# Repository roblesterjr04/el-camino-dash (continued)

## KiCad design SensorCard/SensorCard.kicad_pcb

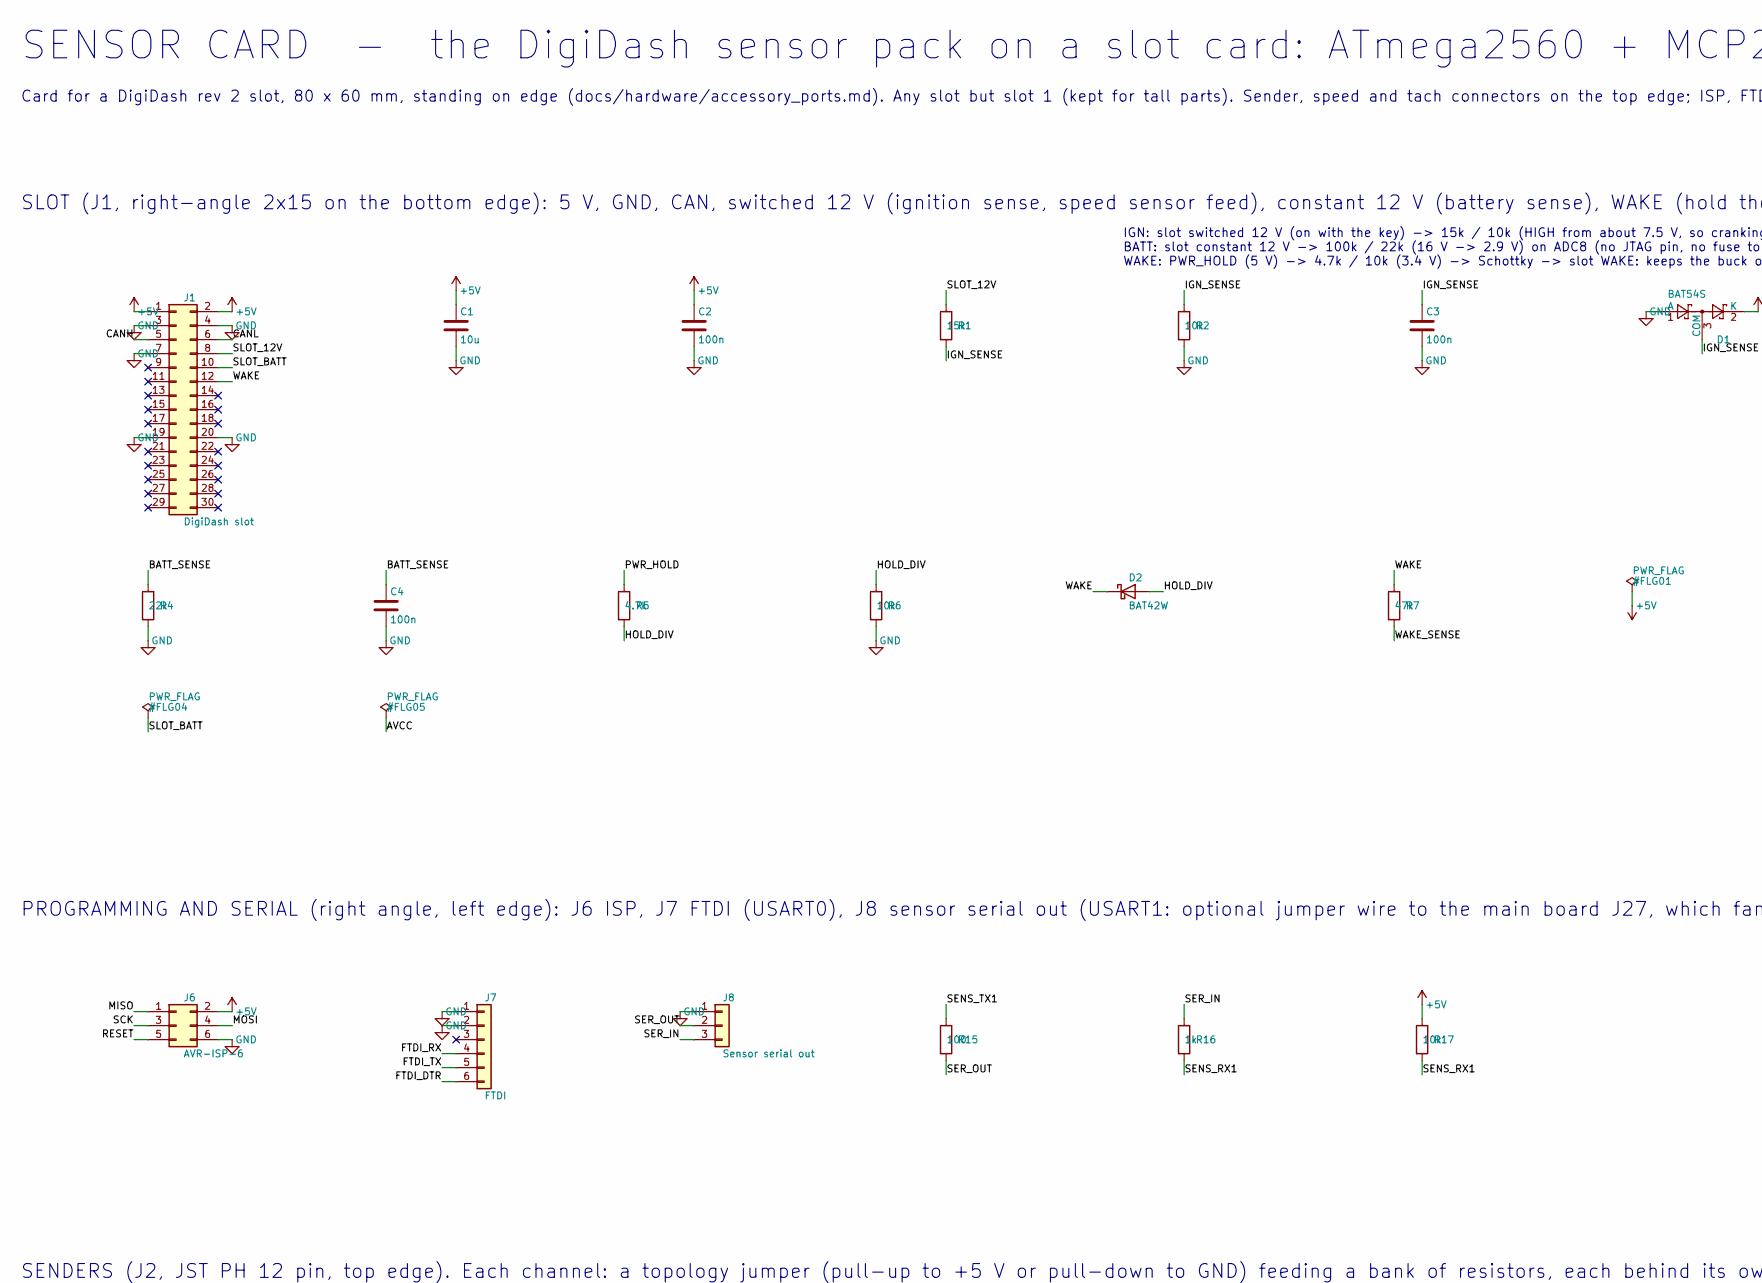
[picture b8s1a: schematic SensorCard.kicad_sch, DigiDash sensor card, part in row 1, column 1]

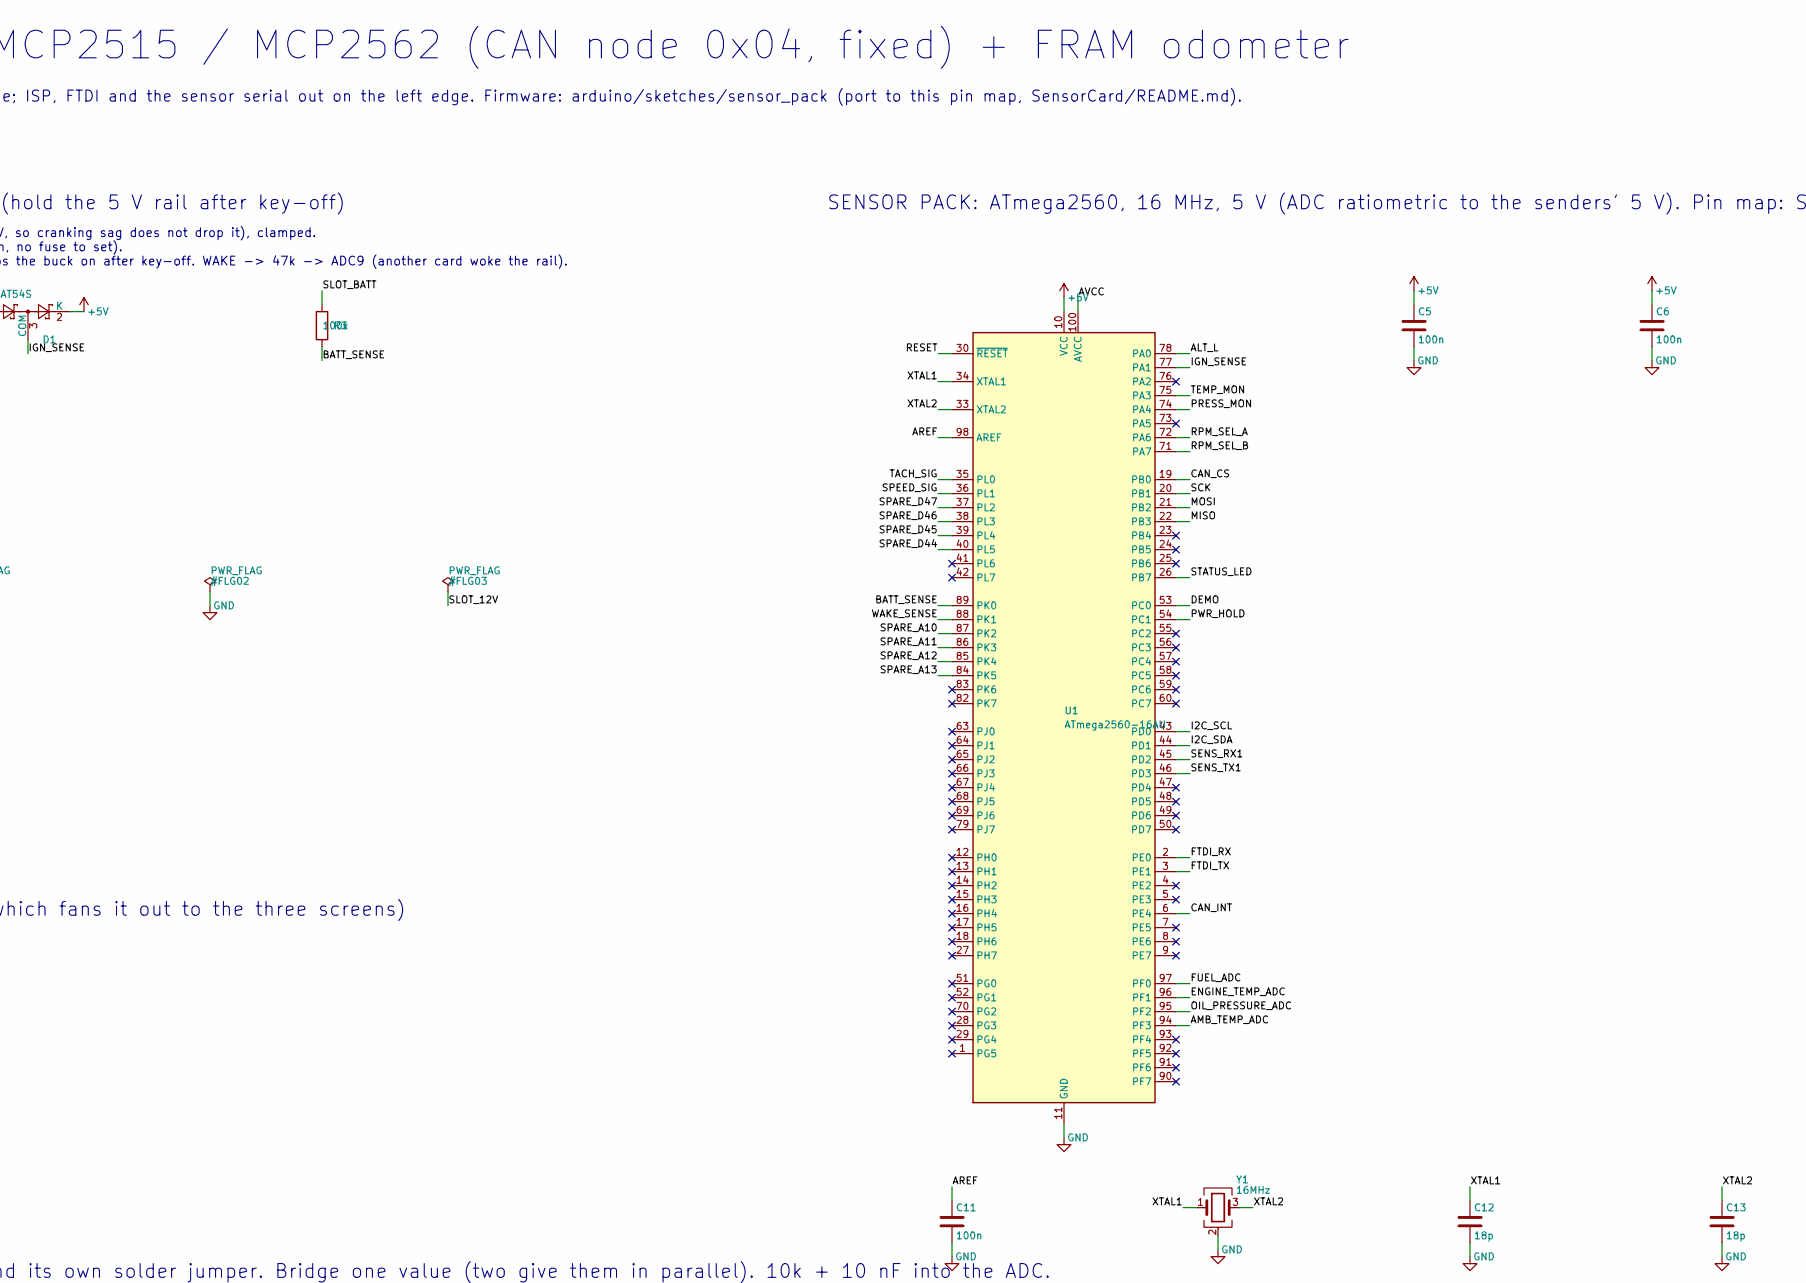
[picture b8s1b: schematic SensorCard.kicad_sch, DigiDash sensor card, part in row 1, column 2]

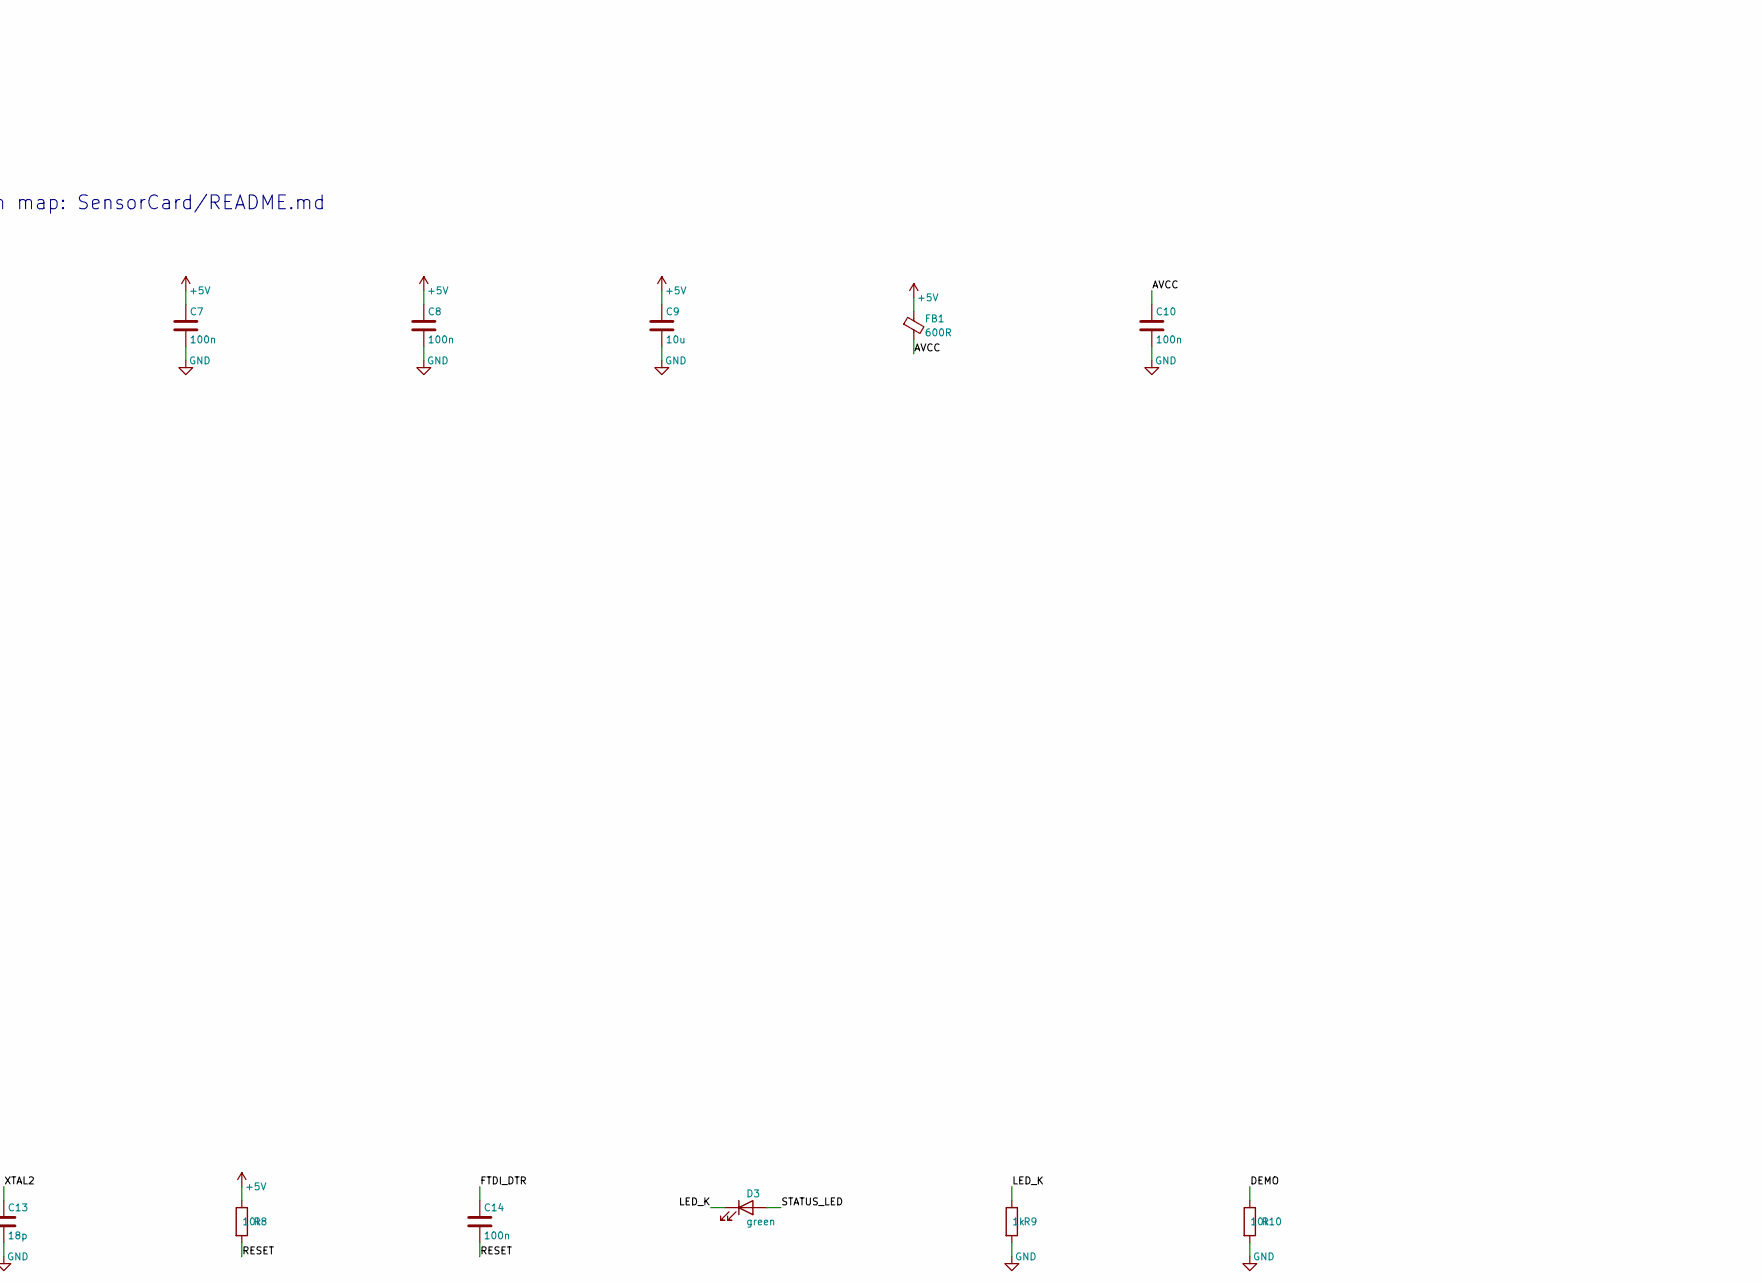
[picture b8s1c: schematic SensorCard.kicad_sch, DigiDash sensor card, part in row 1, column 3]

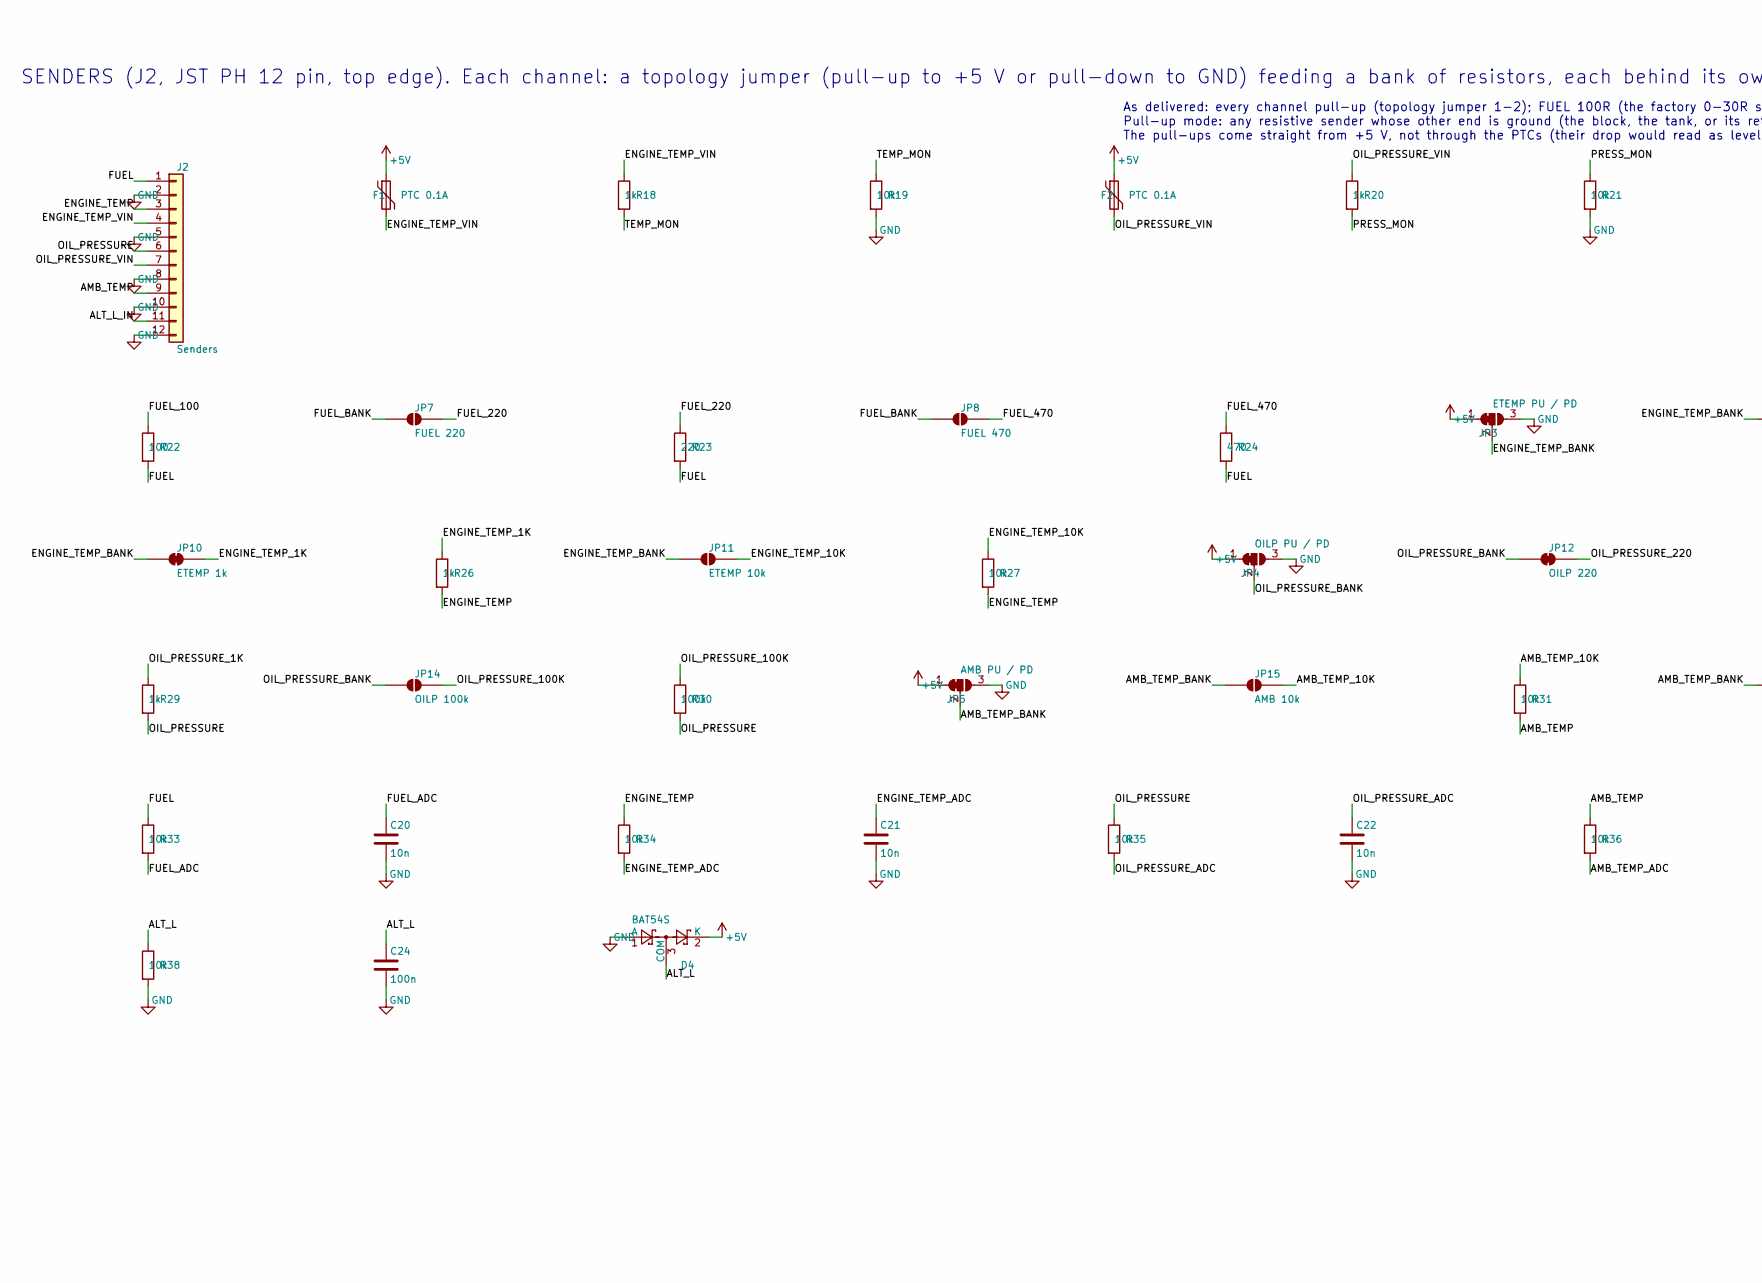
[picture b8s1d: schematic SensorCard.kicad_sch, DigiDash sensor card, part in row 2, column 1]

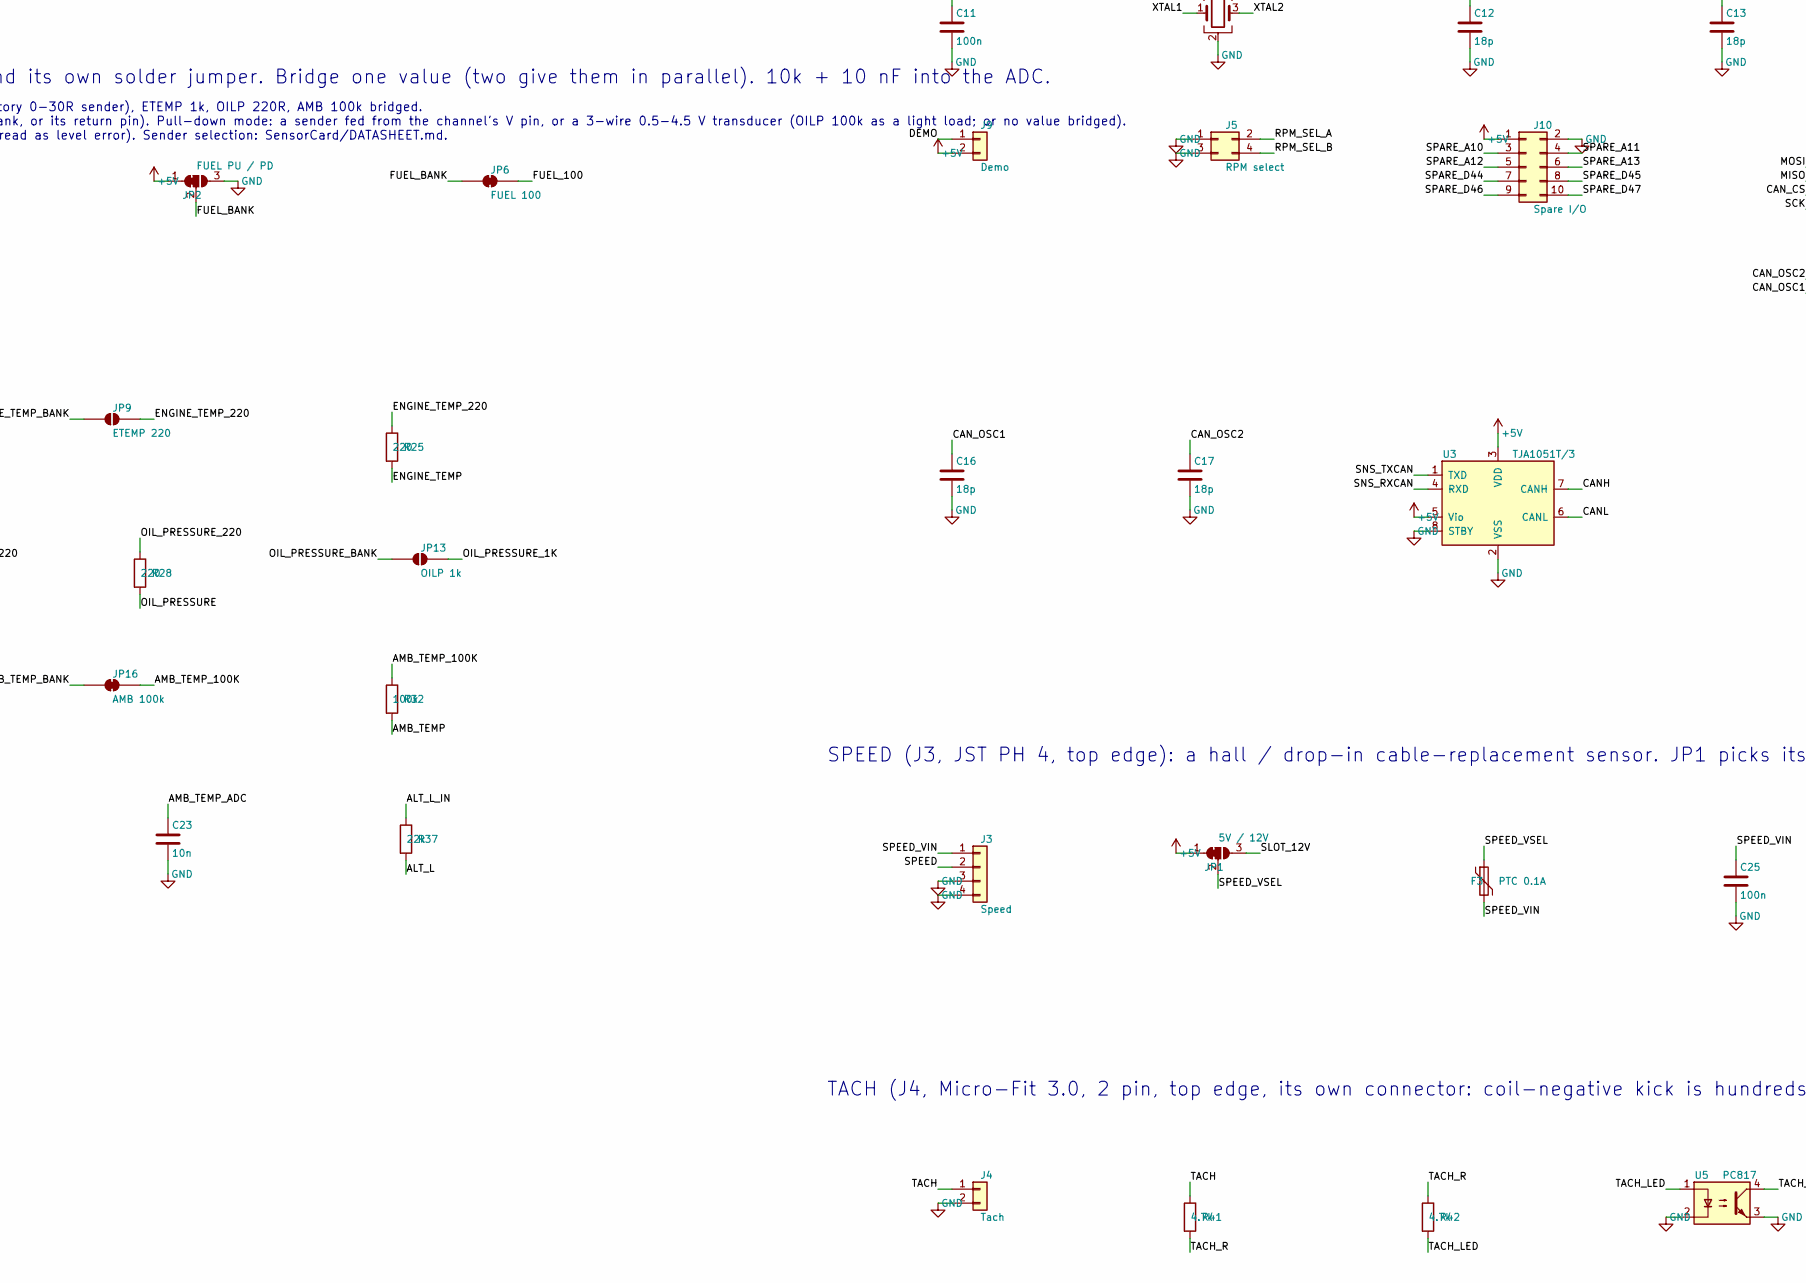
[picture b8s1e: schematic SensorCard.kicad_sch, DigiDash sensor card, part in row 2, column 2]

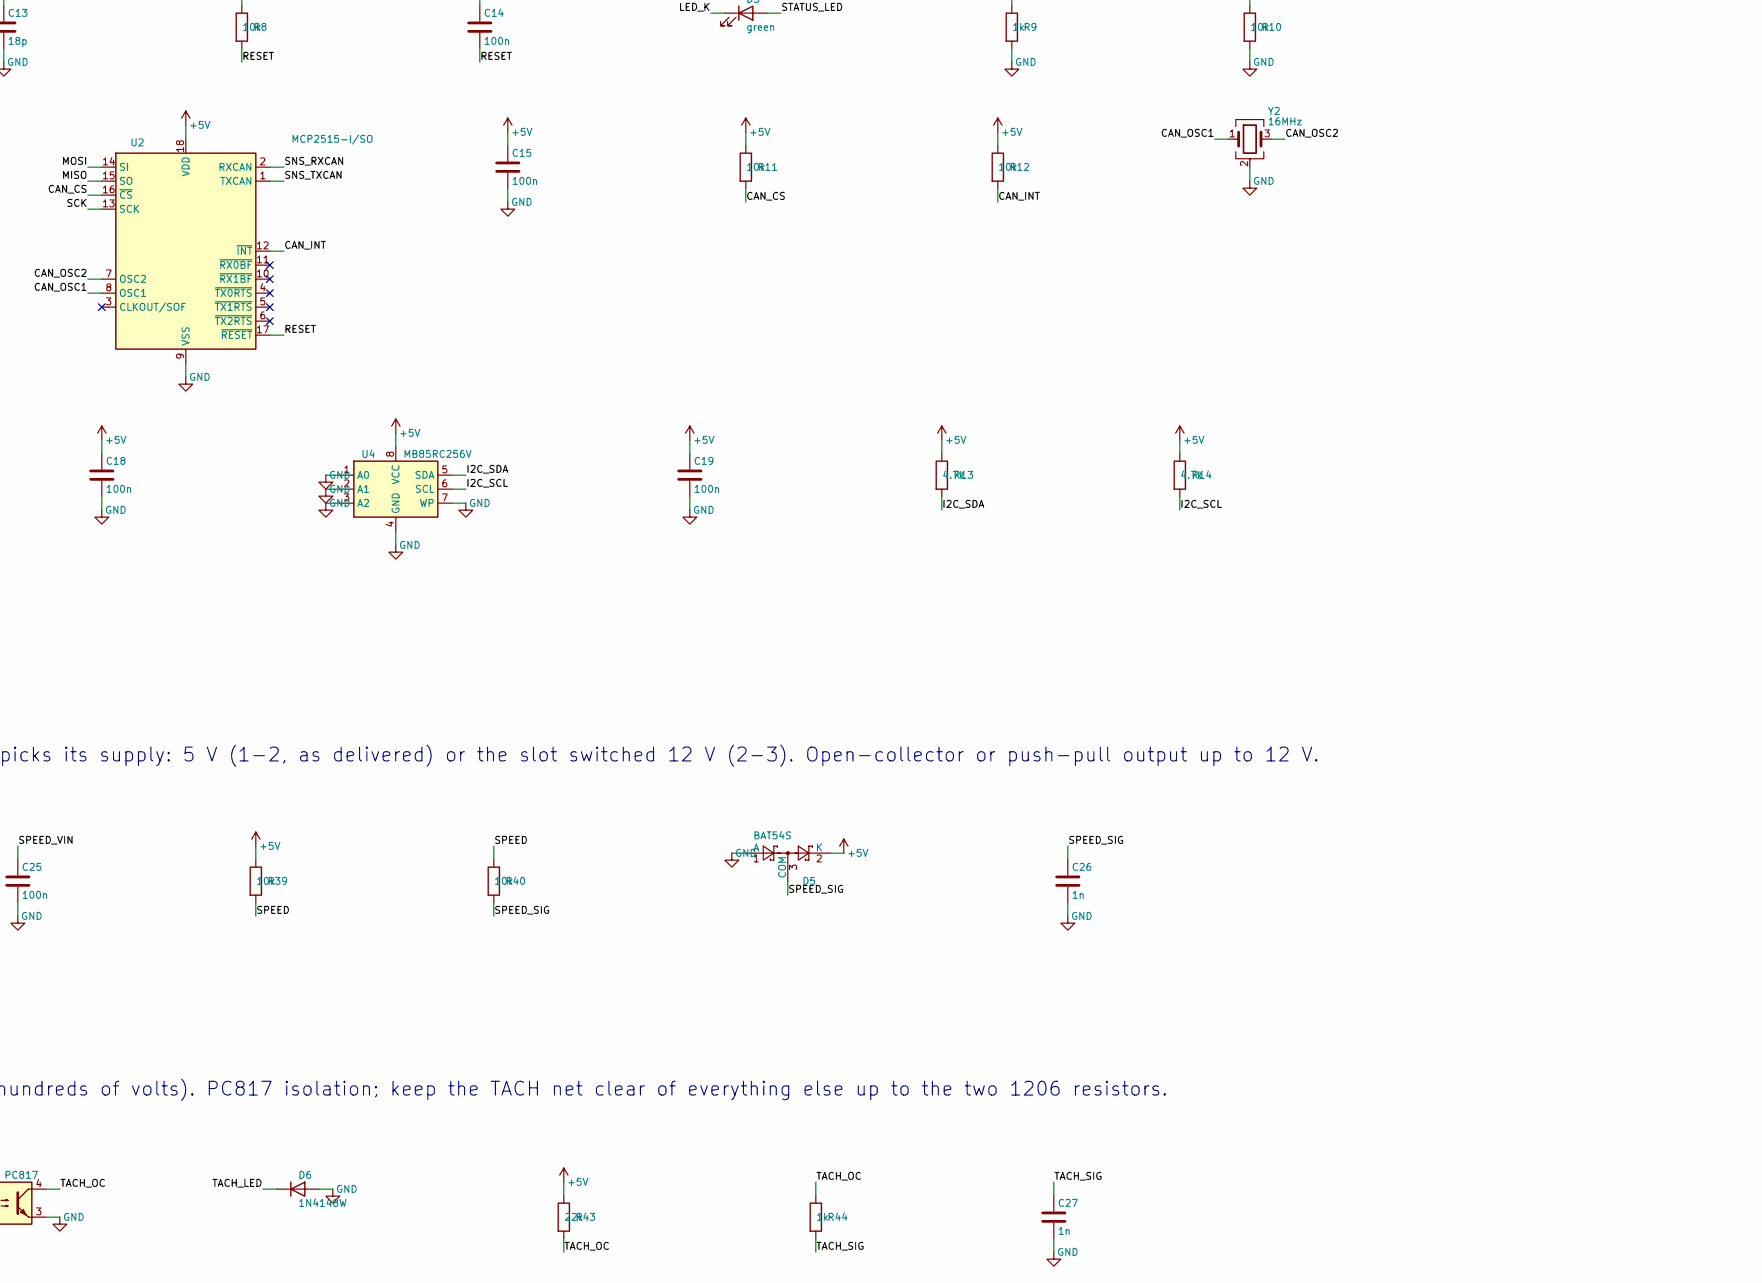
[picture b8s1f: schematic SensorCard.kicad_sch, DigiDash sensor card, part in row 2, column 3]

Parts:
C1, C9: 10u; C_0805_2012Metric
C2, C3, C4, C5, C6, C7, C8, C10, C11, C14, C15, C18, C19, C24: 100n; C_0603_1608Metric
C12, C13, C16, C17: 18p; C_0603_1608Metric
C20, C21, C22, C23: 10n; C_0603_1608Metric
C25: 100n; C_0805_2012Metric
C26, C27: 1n; C_0603_1608Metric
D1, D4, D5: BAT54S; SOT-23
D2: BAT42W; D_SOD-123
D3: green; LED_0603_1608Metric
D6: 1N4148W; D_SOD-123
F1, F2, F3: PTC 0.1A; Fuse_1206_3216Metric
FB1: 600R; L_0603_1608Metric
J1: DigiDash slot; PinHeader_2x15_P2.54mm_Horizontal
J2: Senders; JST_PH_S12B-PH-K_1x12_P2.00mm_Horizontal
J3: Speed; JST_PH_S4B-PH-K_1x04_P2.00mm_Horizontal
J4: Tach; Molex_Micro-Fit_3.0_43650-0200_1x02_P3.00mm_Horizontal
J5: RPM select; PinHeader_2x02_P2.54mm_Vertical
J6: AVR-ISP-6; PinHeader_2x03_P2.54mm_Horizontal
J7: FTDI; PinHeader_1x06_P2.54mm_Horizontal
J8: Sensor serial out; PinHeader_1x03_P2.54mm_Horizontal
J9: Demo; PinHeader_1x02_P2.54mm_Vertical
J10: Spare I/O; PinHeader_2x05_P2.54mm_Vertical
JP1: 5V / 12V; SolderJumper-3_P1.3mm_Bridged12_RoundedPad1.0x1.5mm
JP2: FUEL PU / PD; SolderJumper-3_P1.3mm_Bridged12_RoundedPad1.0x1.5mm
JP3: ETEMP PU / PD; SolderJumper-3_P1.3mm_Bridged12_RoundedPad1.0x1.5mm
JP4: OILP PU / PD; SolderJumper-3_P1.3mm_Bridged12_RoundedPad1.0x1.5mm
JP5: AMB PU / PD; SolderJumper-3_P1.3mm_Bridged12_RoundedPad1.0x1.5mm
JP6: FUEL 100; SolderJumper-2_P1.3mm_Bridged_RoundedPad1.0x1.5mm
JP7: FUEL 220; SolderJumper-2_P1.3mm_Open_RoundedPad1.0x1.5mm
JP8: FUEL 470; SolderJumper-2_P1.3mm_Open_RoundedPad1.0x1.5mm
JP9: ETEMP 220; SolderJumper-2_P1.3mm_Open_RoundedPad1.0x1.5mm
JP10: ETEMP 1k; SolderJumper-2_P1.3mm_Bridged_RoundedPad1.0x1.5mm
JP11: ETEMP 10k; SolderJumper-2_P1.3mm_Open_RoundedPad1.0x1.5mm
JP12: OILP 220; SolderJumper-2_P1.3mm_Bridged_RoundedPad1.0x1.5mm
JP13: OILP 1k; SolderJumper-2_P1.3mm_Open_RoundedPad1.0x1.5mm
JP14: OILP 100k; SolderJumper-2_P1.3mm_Open_RoundedPad1.0x1.5mm
JP15: AMB 10k; SolderJumper-2_P1.3mm_Open_RoundedPad1.0x1.5mm
JP16: AMB 100k; SolderJumper-2_P1.3mm_Bridged_RoundedPad1.0x1.5mm
R1: 15k; R_0603_1608Metric
R2, R6, R8, R10, R11, R12, R17, R19, R21, R27, R31, R33, R34, R35, R36, R38, R39, R40: 10k; R_0603_1608Metric
R3, R30, R32: 100k; R_0603_1608Metric
R4, R37, R43: 22k; R_0603_1608Metric
R5, R13, R14: 4.7k; R_0603_1608Metric
R7: 47k; R_0603_1608Metric
R9, R16, R18, R20, R26, R29, R44: 1k; R_0603_1608Metric
R15: 100; R_0603_1608Metric
R22: 100; R_2010_5025Metric
R23, R25, R28: 220; R_1206_3216Metric
R24: 470; R_0805_2012Metric
R41, R42: 4.7k; R_1206_3216Metric
U1: ATmega2560-16AU; TQFP-100_14x14mm_P0.5mm
U2: MCP2515-I/SO; SOIC-18W_7.5x11.6mm_P1.27mm
U3: TJA1051T/3; SOIC-8_3.9x4.9mm_P1.27mm
U4: MB85RC256V; SOIC-8_3.9x4.9mm_P1.27mm
U5: PC817; SMDIP-4_W7.62mm
Y1, Y2: 16MHz; Crystal_SMD_3225-4Pin_3.2x2.5mm

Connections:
+5V: C1.1, C2.1, C5.1, C6.1, C7.1, C8.1, C9.1, C15.1, C18.1, C19.1, D1.2 (K), D4.2 (K), D5.2 (K), F1.1, F2.1, FB1.1, J1.1, J1.2, J6.2, J9.2, J10.1, JP1.1 (A), JP2.1 (A), JP3.1 (A), JP4.1 (A), JP5.1 (A), R8.1, R11.1, R12.1, R13.1, R14.1, R17.1, R39.1, R43.1, U1.10 (VCC), U1.31 (VCC), U1.61 (VCC), U1.80 (VCC), U2.18 (VDD), U3.3 (VDD), U3.5 (Vio), U4.8 (VCC)
/ALT_L: C24.1, D4.3 (COM), R37.2, R38.1, U1.78 (PA0)
/ALT_L_IN: J2.11, R37.1
/AMB_TEMP: J2.9, R31.2, R32.2, R36.1
/AMB_TEMP_10K: JP15.2 (B), R31.1
/AMB_TEMP_100K: JP16.2 (B), R32.1
/AMB_TEMP_ADC: C23.1, R36.2, U1.94 (PF3)
/AMB_TEMP_BANK: JP5.2 (C), JP15.1 (A), JP16.1 (A)
/AREF: C11.1, U1.98 (AREF)
/AVCC: C10.1, FB1.2, U1.100 (AVCC)
/BATT_SENSE: C4.1, R3.2, R4.1, U1.89 (PK0)
/CANH: J1.5, U3.7 (CANH)
/CANL: J1.6, U3.6 (CANL)
/CAN_CS: R11.2, U1.19 (PB0), U2.16 (~CS)
/CAN_INT: R12.2, U1.6 (PE4), U2.12 (~INT)
/CAN_OSC1: C16.1, U2.8 (OSC1), Y2.1
/CAN_OSC2: C17.1, U2.7 (OSC2), Y2.3
/DEMO: J9.1, R10.1, U1.53 (PC0)
/ENGINE_TEMP: J2.3, R25.2, R26.2, R27.2, R34.1
/ENGINE_TEMP_1K: JP10.2 (B), R26.1
/ENGINE_TEMP_10K: JP11.2 (B), R27.1
/ENGINE_TEMP_220: JP9.2 (B), R25.1
/ENGINE_TEMP_ADC: C21.1, R34.2, U1.96 (PF1)
/ENGINE_TEMP_BANK: JP3.2 (C), JP9.1 (A), JP10.1 (A), JP11.1 (A)
/ENGINE_TEMP_VIN: F1.2, J2.4, R18.1
/FTDI_DTR: C14.1, J7.6
/FTDI_RX: J7.4, U1.2 (PE0)
/FTDI_TX: J7.5, U1.3 (PE1)
/FUEL: J2.1, R22.2, R23.2, R24.2, R33.1
/FUEL_100: JP6.2 (B), R22.1
/FUEL_220: JP7.2 (B), R23.1
/FUEL_470: JP8.2 (B), R24.1
/FUEL_ADC: C20.1, R33.2, U1.97 (PF0)
/FUEL_BANK: JP2.2 (C), JP6.1 (A), JP7.1 (A), JP8.1 (A)
/HOLD_DIV: D2.2 (A), R5.2, R6.1
/I2C_SCL: R14.2, U1.43 (PD0), U4.6 (SCL)
/I2C_SDA: R13.2, U1.44 (PD1), U4.5 (SDA)
/IGN_SENSE: C3.1, D1.3 (COM), R1.2, R2.1, U1.77 (PA1)
/LED_K: D3.1 (K), R9.1
/MISO: J6.1, U1.22 (PB3), U2.15 (SO)
/MOSI: J6.4, U1.21 (PB2), U2.14 (SI)
/OIL_PRESSURE: J2.6, R28.2, R29.2, R30.2, R35.1
/OIL_PRESSURE_1K: JP13.2 (B), R29.1
/OIL_PRESSURE_100K: JP14.2 (B), R30.1
/OIL_PRESSURE_220: JP12.2 (B), R28.1
/OIL_PRESSURE_ADC: C22.1, R35.2, U1.95 (PF2)
/OIL_PRESSURE_BANK: JP4.2 (C), JP12.1 (A), JP13.1 (A), JP14.1 (A)
/OIL_PRESSURE_VIN: F2.2, J2.7, R20.1
/PRESS_MON: R20.2, R21.1, U1.74 (PA4)
/PWR_HOLD: R5.1, U1.54 (PC1)
/RESET: C14.2, J6.5, R8.2, U1.30 (~RESET), U2.17 (~RESET)
/RPM_SEL_A: J5.2, U1.72 (PA6)
/RPM_SEL_B: J5.4, U1.71 (PA7)
/SCK: J6.3, U1.20 (PB1), U2.13 (SCK)
/SENS_RX1: R16.2, R17.2, U1.45 (PD2)
/SENS_TX1: R15.1, U1.46 (PD3)
/SER_IN: J8.3, R16.1
/SER_OUT: J8.2, R15.2
/SLOT_12V: J1.8, JP1.3 (B), R1.1
/SLOT_BATT: J1.10, R3.1
/SNS_RXCAN: U2.2 (RXCAN), U3.4 (RXD)
/SNS_TXCAN: U2.1 (TXCAN), U3.1 (TXD)
/SPARE_A10: J10.3, U1.87 (PK2)
/SPARE_A11: J10.4, U1.86 (PK3)
/SPARE_A12: J10.5, U1.85 (PK4)
/SPARE_A13: J10.6, U1.84 (PK5)
/SPARE_D44: J10.7, U1.40 (PL5)
/SPARE_D45: J10.8, U1.39 (PL4)
/SPARE_D46: J10.9, U1.38 (PL3)
/SPARE_D47: J10.10, U1.37 (PL2)
/SPEED: J3.2, R39.2, R40.1
/SPEED_SIG: C26.1, D5.3 (COM), R40.2, U1.36 (PL1)
/SPEED_VIN: C25.1, F3.2, J3.1
/SPEED_VSEL: F3.1, JP1.2 (C)
/STATUS_LED: D3.2 (A), U1.26 (PB7)
/TACH: J4.1, R41.1
/TACH_LED: D6.1 (K), R42.2, U5.1
/TACH_OC: R43.2, R44.1, U5.4
/TACH_R: R41.2, R42.1
/TACH_SIG: C27.1, R44.2, U1.35 (PL0)
/TEMP_MON: R18.2, R19.1, U1.75 (PA3)
/WAKE: D2.1 (K), J1.12, R7.1
/WAKE_SENSE: R7.2, U1.88 (PK1)
/XTAL1: C12.1, U1.34 (XTAL1), Y1.1
/XTAL2: C13.1, U1.33 (XTAL2), Y1.3
GND: C1.2, C2.2, C3.2, C4.2, C5.2, C6.2, C7.2, C8.2, C9.2, C10.2, C11.2, C12.2, C13.2, C15.2, C16.2, C17.2, C18.2, C19.2, C20.2, C21.2, C22.2, C23.2, C24.2, C25.2, C26.2, C27.2, D1.1 (A), D4.1 (A), D5.1 (A), D6.2 (A), J1.3, J1.4, J1.7, J1.19, J1.20, J2.2, J2.5, J2.8, J2.10, J2.12, J3.3, J3.4, J4.2, J5.1, J5.3, J6.6, J7.1, J7.2, J8.1, J10.2, JP2.3 (B), JP3.3 (B), JP4.3 (B), JP5.3 (B), R2.2, R4.2, R6.2, R9.2, R10.2, R19.2, R21.2, R38.2, U1.11 (GND), U1.32 (GND), U1.62 (GND), U1.81 (GND), U1.99 (GND), U2.9 (VSS), U3.2 (VSS), U3.8 (STBY), U4.1 (A0), U4.2 (A1), U4.3 (A2), U4.4 (GND), U4.7 (WP), U5.2, U5.3, Y1.2 (G), Y1.4 (G), Y2.2 (G), Y2.4 (G)

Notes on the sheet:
SENSOR CARD - the DigiDash sensor pack on a slot card: ATmega2560 + MCP2515 / MCP2562 (CAN node 0x04, fixed) + FRAM odometer
Card for a DigiDash rev 2 slot, 80 x 60 mm, standing on edge (docs/hardware/accessory_ports.md). Any slot but slot 1 (kept for tall parts). Sender, speed and tach connectors on the top edge; ISP, FTDI and the sensor serial out on the left edge. Firmware: arduino/sketches/sensor_pack (port to this p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
SLOT (J1, right-angle 2x15 on the bottom edge): 5 V, GND, CAN, switched 12 V (ignition sense, speed sensor feed), constant 12 V (battery sense), WAKE (hold the 5 V rail after key-off)
IGN: slot switched 12 V (on with the key) -> 15k / 10k (HIGH from about 7.5 V, so cranking sag does not drop it), clamped. BATT: slot constant 12 V -> 100k / 22k (16 V -> 2.9 V) on ADC8 (no JTAG pin, no fuse to set). WAKE: PWR_HOLD (5 V) -> 4.7k / 10k (3.4 V) -> Schottky -> slot WAKE: keeps the buc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
SENSOR PACK: ATmega2560, 16 MHz, 5 V (ADC ratiometric to the senders' 5 V). Pin map: SensorCard/README.md
PROGRAMMING AND SERIAL (right angle, left edge): J6 ISP, J7 FTDI (USART0), J8 sensor serial out (USART1: optional jumper wire to the main board J27, which fans it out to the three screens)
SENDERS (J2, JST PH 12 pin, top edge). Each channel: a topology jumper (pull-up to +5 V or pull-down to GND) feeding a bank of resistors, each behind its own solder jumper. Bridge one value (two give them in parallel). 10k + 10 nF into the ADC.
As delivered: every channel pull-up (topology jumper 1-2); FUEL 100R (the factory 0-30R sender), ETEMP 1k, OILP 220R, AMB 100k bridged. Pull-up mode: any resistive sender whose other end is ground (the block, the tank, or its return pin). Pull-down mode: a sender fed from the channel's V pin, or a 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
SPEED (J3, JST PH 4, top edge): a hall / drop-in cable-replacement sensor. JP1 picks its supply: 5 V (1-2, as delivered) or the slot switched 12 V (2-3). Open-collector or push-pull output up to 12 V.
TACH (J4, Micro-Fit 3.0, 2 pin, top edge, its own connector: coil-negative kick is hundreds of volts). PC817 isolation; keep the TACH net clear of everything else up to the two 1206 resistors.
